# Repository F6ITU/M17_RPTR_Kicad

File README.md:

# M17_RPTR_Kicad
Rough Kicad translation from the original Eagle M17_Repeater

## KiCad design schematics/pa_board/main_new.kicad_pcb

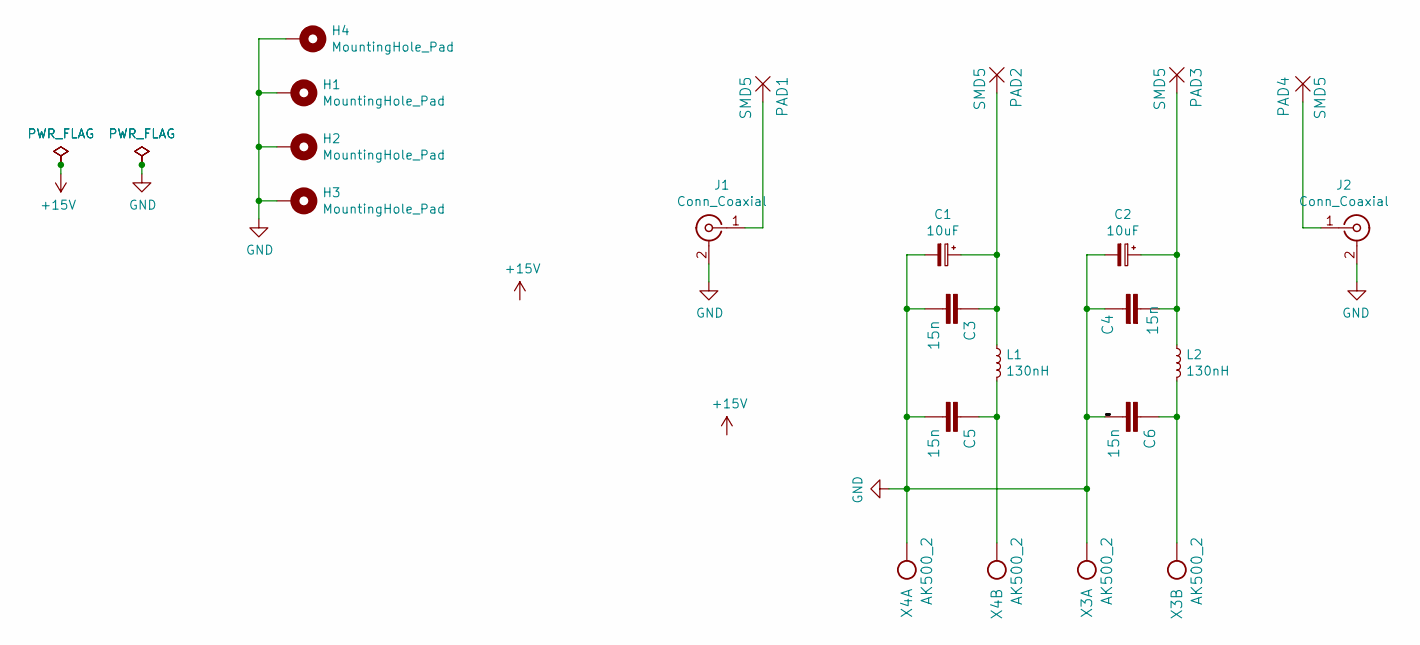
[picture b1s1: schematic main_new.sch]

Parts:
C1, C2: 10uF; CP_EIA-7132-28_AVX-C_Pad2.72x3.50mm_HandSolder
C3, C4, C5, C6: 15n; C_0805_2012Metric_Pad1.15x1.40mm_HandSolder
H1, H2, H3, H4: MountingHole_Pad; MountingHole_3.2mm_M3_ISO7380_Pad
J1, J2: Conn_Coaxial; SMA_EDGE_NRW
L1, L2: 130nH; XEL3520131MEB
PAD1, PAD2, PAD3, PAD4: SMD5; SMD2,54-5,08
X3, X4: AK500_2; TerminalBlock_Phoenix_PT-1,5-2-5.0-H_1x02_P5.00mm_Horizontal

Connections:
GND: C1.2, C2.2, C3.2, C4.1, C5.2, C6.2, H1.1, H2.1, H3.1, H4.1, J1.2 (Ext), J2.2 (Ext), X3.1, X4.1
unnamed: C1.1, C3.1, L1.1, PAD2.1
unnamed: C2.1, C4.2, L2.1, PAD3.1
unnamed: C5.1, L1.2, X4.2
unnamed: C6.1, L2.2, X3.2
unnamed: J1.1 (In), PAD1.1
unnamed: J2.1 (In), PAD4.1

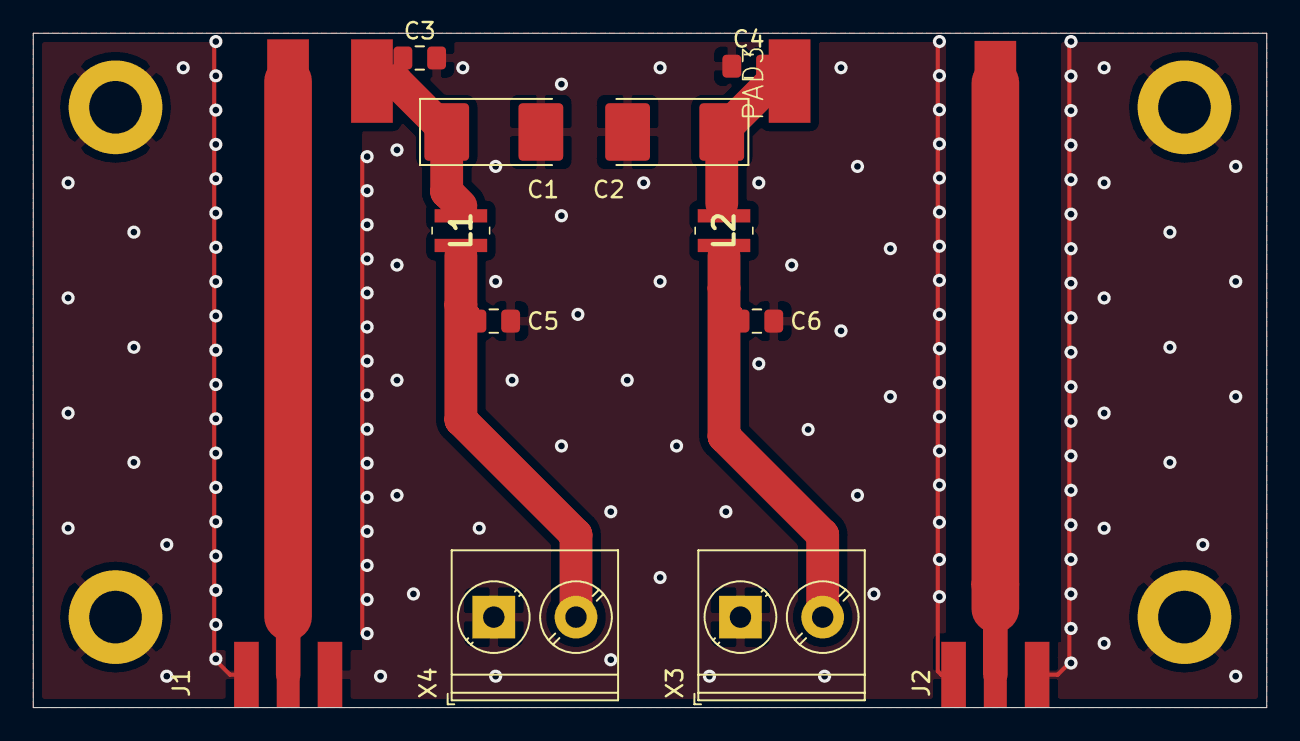
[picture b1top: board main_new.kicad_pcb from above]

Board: 2 copper layers, 75.0 x 41.0 mm, 20 parts (0 on the bottom side), 7 nets.

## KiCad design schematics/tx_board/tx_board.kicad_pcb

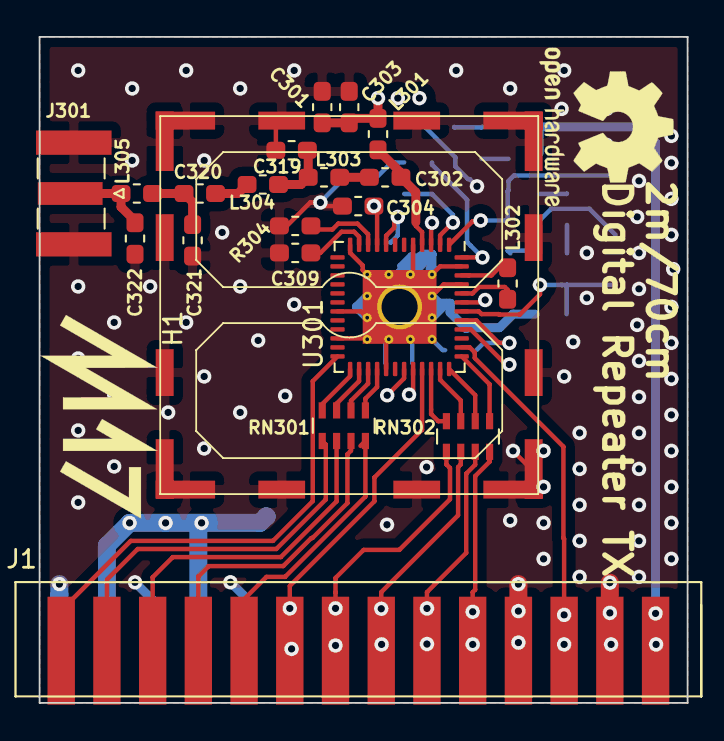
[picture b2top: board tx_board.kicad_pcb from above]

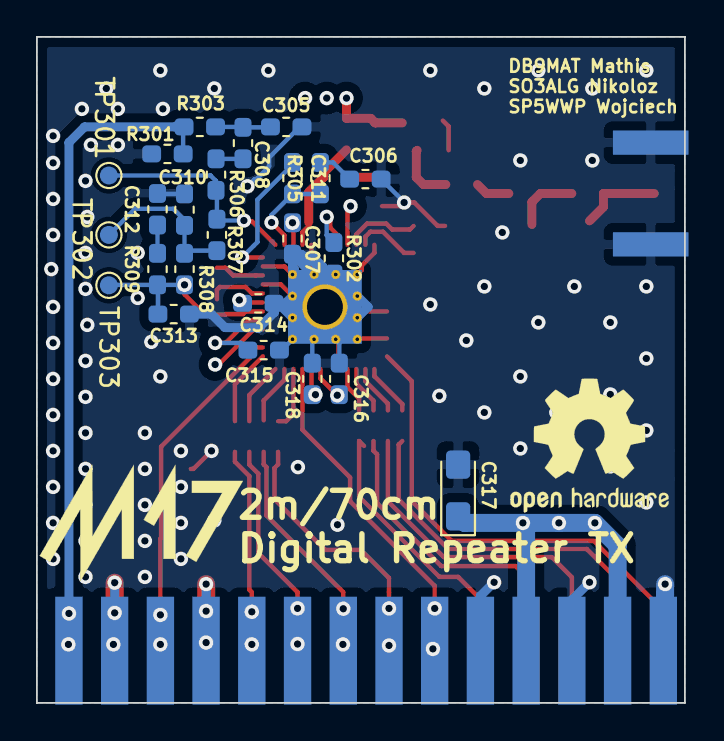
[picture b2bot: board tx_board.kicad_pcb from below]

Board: 4 copper layers, 36.0 x 37.0 mm, 45 parts (24 on the bottom side), 44 nets.

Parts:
C301: 220p; C_0603_1608Metric_Pad1.05x0.95mm_HandSolder
C302: 10p; C_0603_1608Metric_Pad1.05x0.95mm_HandSolder
C303, C304, C307, C314, C318: 10n; C_0603_1608Metric_Pad1.05x0.95mm_HandSolder
C305: 2n2; C_0603_1608Metric_Pad1.05x0.95mm_HandSolder
C306, C308, C309, C315, C316: 100n; C_0603_1608Metric_Pad1.05x0.95mm_HandSolder
C310: 470p; C_0603_1608Metric_Pad1.05x0.95mm_HandSolder
C311: 22n; C_0603_1608Metric_Pad1.05x0.95mm_HandSolder
C312: 15n; C_0603_1608Metric_Pad1.05x0.95mm_HandSolder
C313: 1n; C_0603_1608Metric_Pad1.05x0.95mm_HandSolder
C317: 22u/TA; CP_EIA-3216-18_Kemet-A_Pad1.58x1.35mm_HandSolder
C319: 6p8; C_0603_1608Metric_Pad1.05x0.95mm_HandSolder
C320: 1000p; C_0603_1608Metric_Pad1.05x0.95mm_HandSolder
C321, C322: 9p1; C_0603_1608Metric_Pad1.05x0.95mm_HandSolder
H1: Würt_LGA_Shielding; WE_36103205_SMD
J1: Conn_02x14_Odd_Even; edge_2x14pin
J301: Out; SMA_Samtec_SMA-J-P-X-ST-EM1_EdgeMount
L301: 15n; L_0603_1608Metric_Pad1.05x0.95mm_HandSolder
L302: DNP; L_0603_1608Metric_Pad1.05x0.95mm_HandSolder
L303: 20n; L_0603_1608Metric_Pad1.05x0.95mm_HandSolder
L304: 22n; L_0603_1608Metric_Pad1.05x0.95mm_HandSolder
L305: 15nH; L_0603_1608Metric_Pad1.05x0.95mm_HandSolder
R301: 22k; R_0603_1608Metric_Pad1.05x0.95mm_HandSolder
R302: 1k1; R_0603_1608Metric_Pad1.05x0.95mm_HandSolder
R303, R306: 47k; R_0603_1608Metric_Pad1.05x0.95mm_HandSolder
R304: 3k6; R_0603_1608Metric_Pad1.05x0.95mm_HandSolder
R305: 3R9; R_0603_1608Metric_Pad1.05x0.95mm_HandSolder
R307: 100; R_0603_1608Metric_Pad1.05x0.95mm_HandSolder
R308: 560; R_0603_1608Metric_Pad1.05x0.95mm_HandSolder
R309: 270; R_0603_1608Metric_Pad1.05x0.95mm_HandSolder
RN301, RN302: 4 x 1k ISOLATED; R_Array_Concave_4x0603
TP301, TP302, TP303: TestPoint_Probe; TestPoint_Pad_D1.0mm
U301: ADF7021; LFCSP-48-1EP_7x7mm_P0.5mm_EP4.1x4.1mm_ThermalVias

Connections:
+3V3: C301.1, C303.1, C304.1, C307.1, C314.1, C317.1, C318.1, J1.4, J1.8, L301.1, U301.3, U301.9, U301.32, U301.40, U301.43
ADF_CE: J1.1, U301.24
ADF_MUXOUT: J1.19, J1.20, RN302.8
ADF_SCLK: J1.9, RN301.8
ADF_SDATA: J1.5, RN301.6
ADF_SLE: J1.3, RN301.5
ADF_SREAD: J1.7, RN301.7
ADF_SWD: J1.11, J1.12, U301.33
EXT_OSC2_IN: J1.23, J1.24, U301.38
FM_MOD: J1.27, J1.28, R301.2, R303.1
GND: C301.2, C303.2, C304.2, C305.1, C306.2, C307.2, C309.2, C310.2, C312.2, C313.2, C314.2, C315.2, C316.1, C317.2, C318.2, C319.2, C321.1, C322.1, H1.1, J1.2, J1.6, J1.10, J1.21, J1.22, J1.25, J1.26, J301.2, R301.1, R302.2, R304.2, U301.5, U301.12, U301.19, U301.22, U301.29, U301.45, U301.47, U301.49
unnamed: C302.2, L301.2, U301.4
unnamed: C305.2, C308.2, R303.2
unnamed: C306.1, R305.2
unnamed: C308.1, R306.2
unnamed: C309.1, U301.11
unnamed: C310.1, R307.1, R308.2, TP302.1
unnamed: C311.1, U301.48
unnamed: C311.2, R305.1, U301.2
unnamed: C312.1, R309.2
unnamed: C313.1, R308.1, R309.1, TP303.1, U301.42
unnamed: C315.1, U301.41
unnamed: C316.2, U301.31
unnamed: C319.1, L303.2, L304.1
unnamed: C320.1, C321.2, L305.1
unnamed: C320.2, L304.2
unnamed: C322.2, J301.1, L305.2
unnamed: L302.1, U301.46
unnamed: L302.2, U301.44
unnamed: R302.1, U301.8
unnamed: R304.1, U301.10
unnamed: R306.1, R307.2, TP301.1, U301.1
unnamed: RN301.1, U301.28
unnamed: RN301.2, U301.27
unnamed: RN301.3, U301.26
unnamed: RN301.4, U301.25
unnamed: RN302.1, U301.37
unnamed: RN302.2, U301.36
unnamed: RN302.3, U301.35
unnamed: RN302.4, U301.34
SPI2_MISO: J1.15, J1.16, RN302.6
SPI2_MOSI: J1.13, J1.14, RN302.5
SPI2_SCK: J1.17, J1.18, RN302.7
TX: C302.1, L303.1

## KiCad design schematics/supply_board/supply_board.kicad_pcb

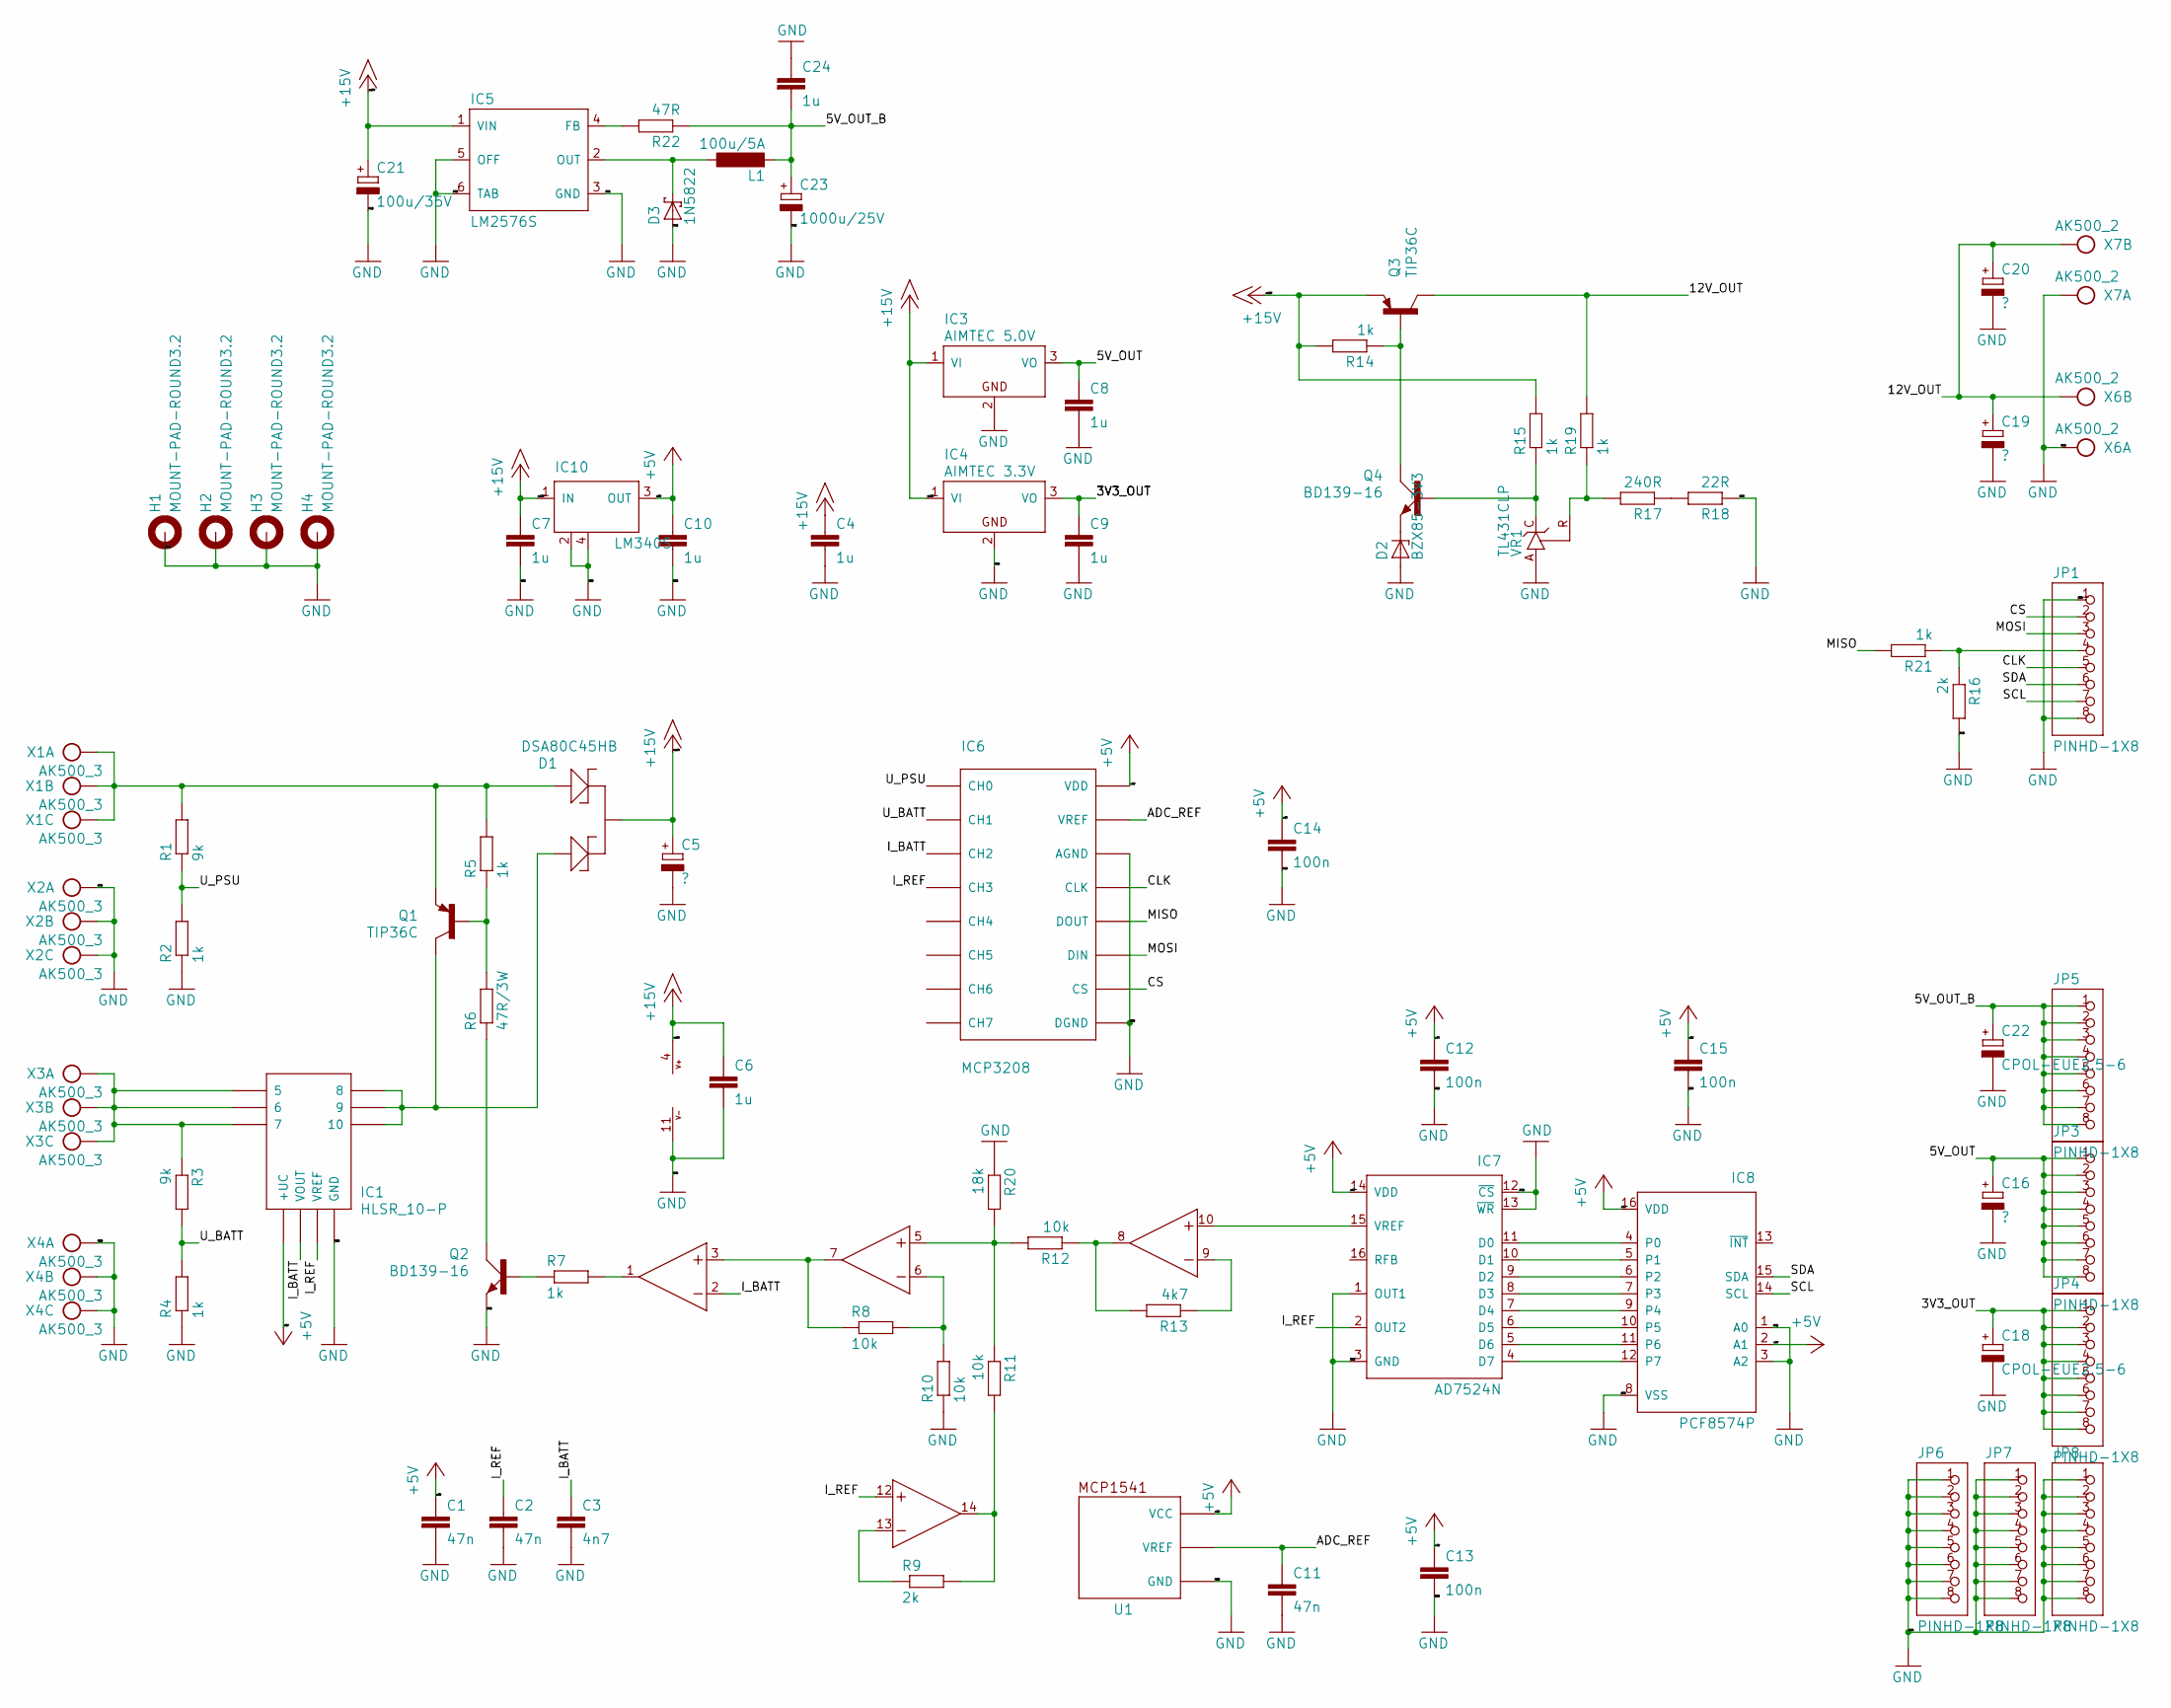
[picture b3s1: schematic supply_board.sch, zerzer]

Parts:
C1, C2, C11: 47n; C0805
C3: 4n7; C0805
C4, C6, C7, C8, C9, C10, C24: 1u; C0805
C5, C19, C20: ?; E5-13
C12, C13, C14, C15: 100n; C0805
C16: ?; E2,5-6
C18, C22: CPOL-EUE2.5-6; E2,5-6
C21: 100u/35V; E5-10,5
C23: 1000u/25V; E5-10,5
D1: DSA80C45HB; TO247BV
D2: BZX85-3V3; DO41Z10
D3: 1N5822; C4111-15
H1, H2, H3, H4: MOUNT-PAD-ROUND3.2; 3,2-PAD
IC1: HLSR_10-P; HLSR16-P
IC2: LM324N; DIL14
IC3: AIMTEC 5.0V; TO220V
IC4: AIMTEC 3.3V; TO220V
IC5: LM2576S; TO263-5
IC6: MCP3208; DIL16
IC7: AD7524N; DIL16
IC8: PCF8574P; DIL16
IC10: LM340S; SOT223
JP1, JP3, JP4, JP5, JP6, JP7, JP8: PINHD-1X8; 1X08
L1: 100u/5A; TJ5-U2
Q1, Q3: TIP36C; TO247-V
Q2, Q4: BD139-16; TO126AV
R1, R3: 9k; R0805
R2, R4, R5, R7, R14, R15, R19, R21: 1k; R0805
R6: 47R/3W; 0617_22
R8, R10, R11, R12: 10k; R0805
R9, R16: 2k; R0805
R13: 4k7; R0805
R17: 240R; R0805
R18: 22R; R0805
R20: 18k; R0805
R22: 47R; R0805
U1: VOLT_REFERENCE; SOT23
VR1: TL431CLP; TO92-CLP
X1, X2, X3, X4: AK500_3
X6, X7: AK500_2

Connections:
+5V: C1.1, C10.1, C12.1, C13.1, C14.1, C15.1, IC1.4 (+UC), IC6.VDD, IC7.14 (VDD), IC8.2 (A1), IC8.16 (VDD), IC10.3 (OUT), U1.1 (VCC)
+15V: C4.1, C5.+, C6.1, C7.1, C21.+, D1.2, IC2.4 (V+), IC3.1 (VI), IC4.1 (VI), IC5.1 (VIN), IC10.1 (IN), Q3.3 (E), R14.2, R15.2
/3V3_OUT: C9.1, C18.+, IC4.3 (VO), JP4.1, JP4.2, JP4.3, JP4.4, JP4.5, JP4.6, JP4.7, JP4.8
/5V_OUT: C8.1, C16.+, IC3.3 (VO), JP3.1, JP3.2, JP3.3, JP3.4, JP3.5, JP3.6, JP3.7, JP3.8
/5V_OUT_B: C22.+, C23.+, C24.2, JP5.1, JP5.2, JP5.3, JP5.4, JP5.5, JP5.6, JP5.7, JP5.8, L1.2, R22.1
/12V_OUT: C19.+, C20.+, Q3.2 (C), R19.2, X6.2, X7.2
/ADC_REF: C11.1, IC6.VREF, U1.2 (VREF)
/CLK: IC6.CLK, JP1.5
/CS: IC6.CS, JP1.2
/I_BATT: C3.1, IC1.2 (VOUT), IC2.2 (-IN), IC6.CH2
/I_REF: C2.1, IC1.1 (VREF), IC2.12 (+IN), IC6.CH3, IC7.2 (OUT2)
/MISO: IC6.DOUT, R21.2
/MOSI: IC6.DIN, JP1.3
/SCL: IC8.14 (SCL), JP1.7
/SDA: IC8.15 (SDA), JP1.6
/U_BATT: IC6.CH1, R3.2, R4.2
/U_PSU: IC6.CH0, R1.1, R2.2
GND: C1.2, C2.2, C3.2, C4.2, C5.-, C6.2, C7.2, C8.2, C9.2, C10.2, C11.2, C12.2, C13.2, C14.2, C15.2, C16.-, C18.-, C19.-, C20.-, C21.-, C22.-, C23.-, C24.1, D2.A, D3.A, H1.B3,2, H2.B3,2, H3.B3,2, H4.B3,2, IC1.3 (GND), IC2.11 (V-), IC3.2 (GND), IC4.2 (GND), IC5.3 (GND), IC5.5 (OFF), IC5.6 (TAB), IC6.AGND, IC6.DGND, IC7.1 (OUT1), IC7.3 (GND), IC7.12 (~CS), IC7.13 (~WR), IC8.1 (A0), IC8.3 (A2), IC8.8 (VSS), IC10.2 (GND@1), IC10.4 (GND@2), JP1.1, JP1.8, JP6.1, JP6.2, JP6.3, JP6.4, JP6.5, JP6.6, JP6.7, JP6.8, JP7.1, JP7.2, JP7.3, JP7.4, JP7.5, JP7.6, JP7.7, JP7.8, JP8.1, JP8.2, JP8.3, JP8.4, JP8.5, JP8.6, JP8.7, JP8.8, Q2.E, R2.1, R4.1, R10.1, R16.2, R18.1, R20.1, U1.3 (GND), VR1.A, X2.1, X2.2, X2.3, X4.1, X4.2, X4.3, X6.1, X7.1
unnamed: D1.1, Q1.3 (E), R1.2, R5.2, X1.1, X1.2, X1.3
unnamed: D1.3, IC1.8, IC1.9, IC1.10, Q1.2 (C)
unnamed: D2.C, Q4.E
unnamed: D3.C, IC5.2 (OUT), L1.1
unnamed: IC1.5, IC1.6, IC1.7, R3.1, X3.1, X3.2, X3.3
unnamed: IC2.1 (OUT), R7.2
unnamed: IC2.3 (+IN), IC2.7 (OUT), R8.1
unnamed: IC2.5 (+IN), R11.1, R12.2, R20.2
unnamed: IC2.6 (-IN), R8.2, R10.2
unnamed: IC2.8 (OUT), R12.1, R13.2
unnamed: IC2.9 (-IN), R13.1
unnamed: IC2.10 (+IN), IC7.15 (VREF)
unnamed: IC2.13 (-IN), R9.1
unnamed: IC2.14 (OUT), R9.2, R11.2
unnamed: IC5.4 (FB), R22.2
unnamed: IC7.4 (D7), IC8.12 (P7)
unnamed: IC7.5 (D6), IC8.11 (P6)
unnamed: IC7.6 (D5), IC8.10 (P5)
unnamed: IC7.7 (D4), IC8.9 (P4)
unnamed: IC7.8 (D3), IC8.7 (P3)
unnamed: IC7.9 (D2), IC8.6 (P2)
unnamed: IC7.10 (D1), IC8.5 (P1)
unnamed: IC7.11 (D0), IC8.4 (P0)
unnamed: JP1.4, R16.1, R21.1
unnamed: Q1.1 (B), R5.1, R6.2
unnamed: Q2.B, R7.1
unnamed: Q2.C, R6.1
unnamed: Q3.1 (B), Q4.C, R14.1
unnamed: Q4.B, R15.1, VR1.C
unnamed: R17.1, R18.2
unnamed: R17.2, R19.1, VR1.R

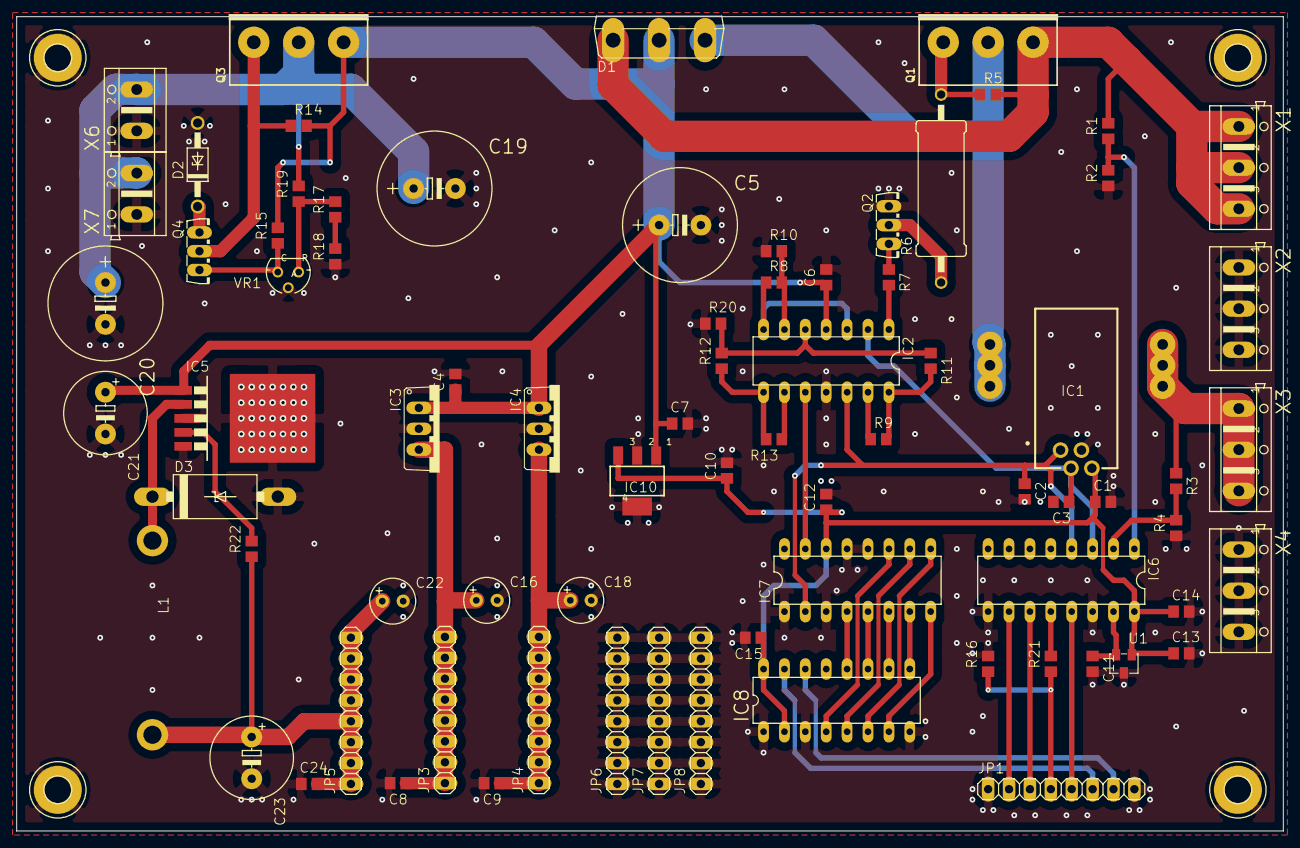
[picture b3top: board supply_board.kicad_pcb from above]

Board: 2 copper layers, 154.0 x 99.0 mm, 81 parts (0 on the bottom side), 49 nets.
